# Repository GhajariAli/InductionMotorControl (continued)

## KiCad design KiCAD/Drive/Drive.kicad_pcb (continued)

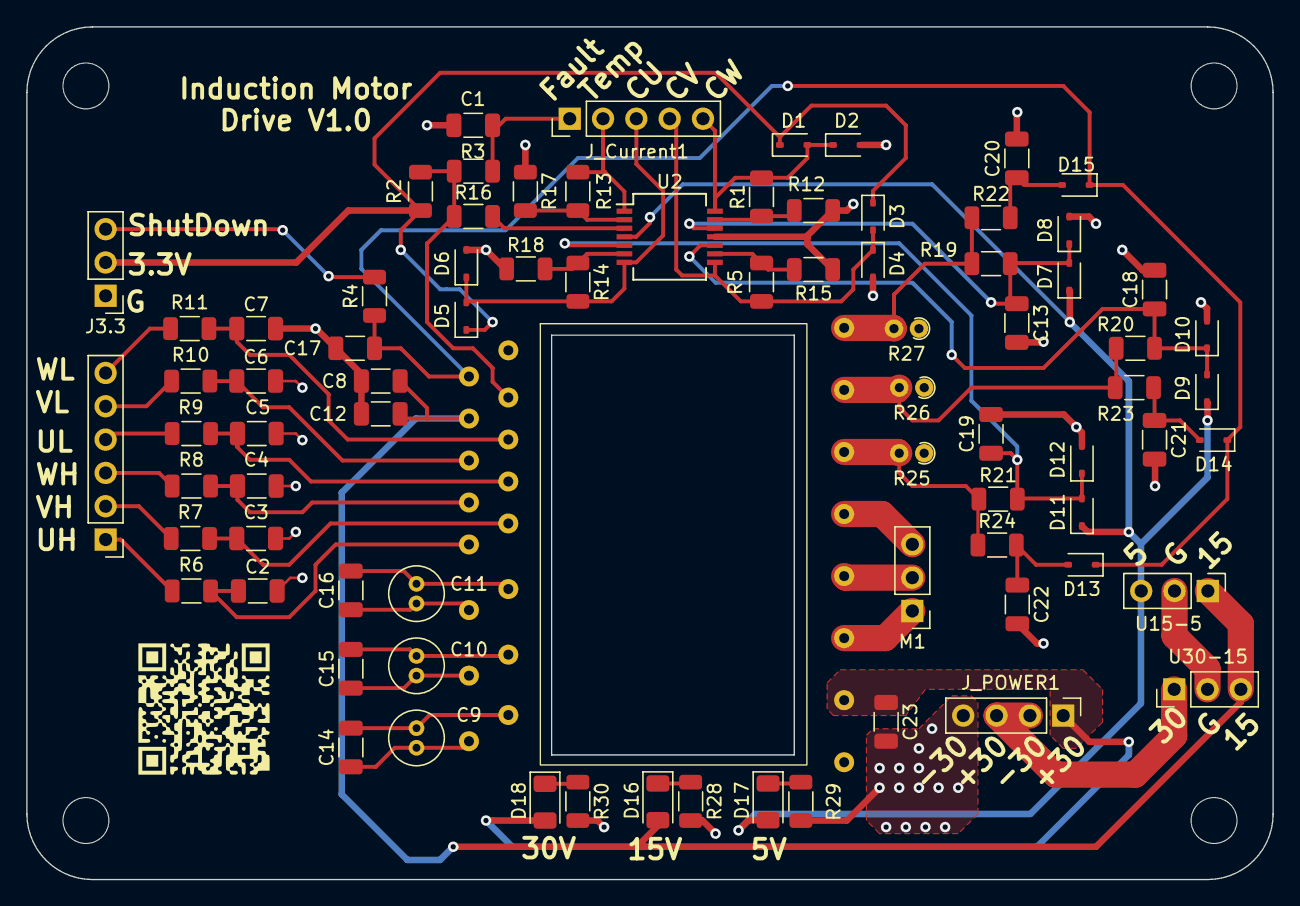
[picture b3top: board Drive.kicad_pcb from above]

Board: 2 copper layers, 95.0 x 65.0 mm, 84 parts (0 on the bottom side), 52 nets.

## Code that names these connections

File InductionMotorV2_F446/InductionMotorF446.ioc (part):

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Mcu.Name=STM32F446R(C-E)Tx
Mcu.Package=LQFP64
Mcu.UserName=STM32F446RETx
PA1.GPIOParameters=GPIO_Label
PA1.GPIO_Label=Drive_Temp
PA1.Signal=ADCx_IN1
PA10.Signal=S_TIM1_CH3
PA11.Mode=Device_Only
PA11.Signal=USB_OTG_FS_DM
PA12.Mode=Device_Only
PA12.Signal=USB_OTG_FS_DP
PA13.Mode=Trace_Asynchronous_SW
PA13.Signal=SYS_JTMS-SWDIO
PA14.Mode=Trace_Asynchronous_SW
PA14.Signal=SYS_JTCK-SWCLK
PA2.Mode=Asynchronous
PA2.Signal=USART2_TX
PA3.Mode=Asynchronous
PA3.Signal=USART2_RX
PA6.GPIOParameters=GPIO_Label
PA6.GPIO_Label=I_U
PA6.Signal=ADCx_IN6
PA7.GPIOParameters=GPIO_Label
PA7.GPIO_Label=I_V
PA7.Signal=ADCx_IN7
PA8.Signal=S_TIM1_CH1
PA9.Signal=S_TIM1_CH2
PB0.GPIOParameters=GPIO_Label
PB0.GPIO_Label=I_W
PB0.Signal=ADCx_IN8
PB1.GPIOParameters=GPIO_Label
PB1.GPIO_Label=I_N
PB1.Signal=ADCx_IN9
PB13.Mode=PWM Generation1 CH1 CH1N
PB13.Signal=TIM1_CH1N
PB14.Mode=PWM Generation2 CH2 CH2N
PB14.Signal=TIM1_CH2N
PB15.Mode=PWM Generation3 CH3 CH3N
PB15.Signal=TIM1_CH3N
PB3.Mode=Trace_Asynchronous_SW
PB3.Signal=SYS_JTDO-SWO
PB6.Mode=Asynchronous
PB6.Signal=USART1_TX
PB7.Mode=Asynchronous
PB7.Signal=USART1_RX
PC0.GPIOParameters=GPIO_PuPd,GPIO_Label
PC0.GPIO_Label=PB1_INT
PC0.GPIO_PuPd=GPIO_PULLDOWN
PC0.Signal=GPXTI0
PC1.GPIOParameters=GPIO_Label
PC1.GPIO_Label=ShutDown
PC1.Signal=GPIO_Output
PC10.GPIOParameters=GPIO_Label
PC10.GPIO_Label=LD1
PC10.Signal=GPIO_Output
PC11.GPIOParameters=GPIO_Label
PC11.GPIO_Label=LD2
PC11.Signal=GPIO_Output
PC12.GPIOParameters=GPIO_Label
PC12.GPIO_Label=LD3
PC12.Signal=GPIO_Output
PC2.GPIOParameters=GPIO_PuPd,GPIO_Label,GPIO_ModeDefaultEXTI
PC2.GPIO_Label=DriveFault_INT
PC2.GPIO_ModeDefaultEXTI=GPIO_MODE_IT_FALLING
PC2.GPIO_PuPd=GPIO_PULLUP
PC2.Signal=GPXTI2
PC3.GPIOParameters=GPIO_Label
PC3.GPIO_Label=Potentiameter
PC3.Signal=ADCx_IN13
PC6.Signal=S_TIM3_CH1
PC7.Signal=S_TIM3_CH2
PH0-OSC_IN.Mode=HSE-External-Clock-Source
PH0-OSC_IN.Signal=RCC_OSC_IN
PH1-OSC_OUT.Mode=HSE-External-Clock-Source
PH1-OSC_OUT.Signal=RCC_OSC_OUT
RCC.HSE_Timout=5000
RCC.HSE_VALUE=20000000
RCC.SYSCLKFreq_VALUE=144000000
RCC.SYSCLKSource=RCC_SYSCLKSOURCE_PLLCLK
board=custom

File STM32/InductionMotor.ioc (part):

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Mcu.Name=STM32F411R(C-E)Tx
Mcu.Package=LQFP64
Mcu.UserName=STM32F411RETx
PA0-WKUP.Signal=S_TIM2_CH1_ETR
PA13.GPIOParameters=GPIO_Label
PA13.GPIO_Label=TMS
PA13.Mode=Serial_Wire
PA13.Signal=SYS_JTMS-SWDIO
PA14.GPIOParameters=GPIO_Label
PA14.GPIO_Label=TCK
PA14.Mode=Serial_Wire
PA14.Signal=SYS_JTCK-SWCLK
PA2.GPIOParameters=GPIO_Label
PA2.GPIO_Label=USART_TX
PA2.Mode=Asynchronous
PA2.Signal=USART2_TX
PA3.GPIOParameters=GPIO_Label
PA3.GPIO_Label=USART_RX
PA3.Mode=Asynchronous
PA3.Signal=USART2_RX
PA5.GPIOParameters=GPIO_Label
PA5.GPIO_Label=LD2 [Green Led]
PA5.Signal=GPIO_Output
PA8.Signal=S_TIM1_CH1
PB3.GPIOParameters=GPIO_Label
PB3.GPIO_Label=SWO
PB3.Signal=SYS_JTDO-SWO
PB9.Signal=S_TIM11_CH1
PC0.Signal=GPIO_Input
PC13-ANTI_TAMP.GPIOParameters=GPIO_Label,GPIO_ModeDefaultEXTI
PC13-ANTI_TAMP.GPIO_Label=B1 [Blue PushButton]
PC13-ANTI_TAMP.GPIO_ModeDefaultEXTI=GPIO_MODE_IT_FALLING
PC13-ANTI_TAMP.Signal=GPXTI13
PC14-OSC32_IN.Mode=LSE-External-Oscillator
PC14-OSC32_IN.Signal=RCC_OSC32_IN
PC15-OSC32_OUT.Mode=LSE-External-Oscillator
PC15-OSC32_OUT.Signal=RCC_OSC32_OUT
PH0\ -\ OSC_IN.Mode=HSE-External-Clock-Source
PH0\ -\ OSC_IN.Signal=RCC_OSC_IN
PH1\ -\ OSC_OUT.Mode=HSE-External-Clock-Source
PH1\ -\ OSC_OUT.Signal=RCC_OSC_OUT
RCC.HSE_VALUE=8000000
RCC.SYSCLKFreq_VALUE=100000000
RCC.SYSCLKSource=RCC_SYSCLKSOURCE_PLLCLK
board=NUCLEO-F411RE
boardIOC=true

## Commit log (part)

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2024-01-02 init
2024-01-02 adds python git ignore
2024-01-02 update gitignore
2024-01-02 sync
2024-01-07 adds circuit diagram
2024-01-12 adds code for motor to run
2024-01-13 adds encoder
2024-01-16 adds oled screen
2024-01-16 sync for Amin
2024-01-18 This Commit might be fucked up
2024-01-21 adds circuit diagram and pcb
2024-01-22 design bug fix
2024-01-22 adds LED function
2024-01-22 adds color funciton
2024-01-22 adds all letters to LED disp
2024-01-26 Motor Running
2024-02-12 testing with PCB
2024-02-13 SPWM Tested
2024-02-14 sequence bug fix
2024-05-04 created spwm function
2024-05-09 added forward reverse state machine
2024-05-15 adds encoder as an EXTI
2024-05-16 adds V/F -WIP
2024-05-24 removed trunc the spwm looks ok now
2024-05-27 made TIM4 a slave of TIM3 and also fixed the freaking 50usec bug!!!!!!!!!!!!!!!!!!!!!!! Sine wave now continues
2024-05-28 VF is ok for now will merge this to master
2024-05-28 code clean up
2024-05-29 put encoder back on timer 2
2024-05-29 Reporting speed and slip on uart to monitor on PC
2024-10-28 mcu swapped with a new one and timers back in order
2024-11-03 finally smooth current shape
2024-11-03 added direction
2024-12-28 drive V2 pcb designed
2025-01-18 V2 tested and working - WIP
2025-01-19 corrects receiver pins
2025-01-19 adds potentiameter to control the speed
2025-04-02 latest sync
2025-08-03 finally fixed ramping up down
2025-08-07 fixed reverse
